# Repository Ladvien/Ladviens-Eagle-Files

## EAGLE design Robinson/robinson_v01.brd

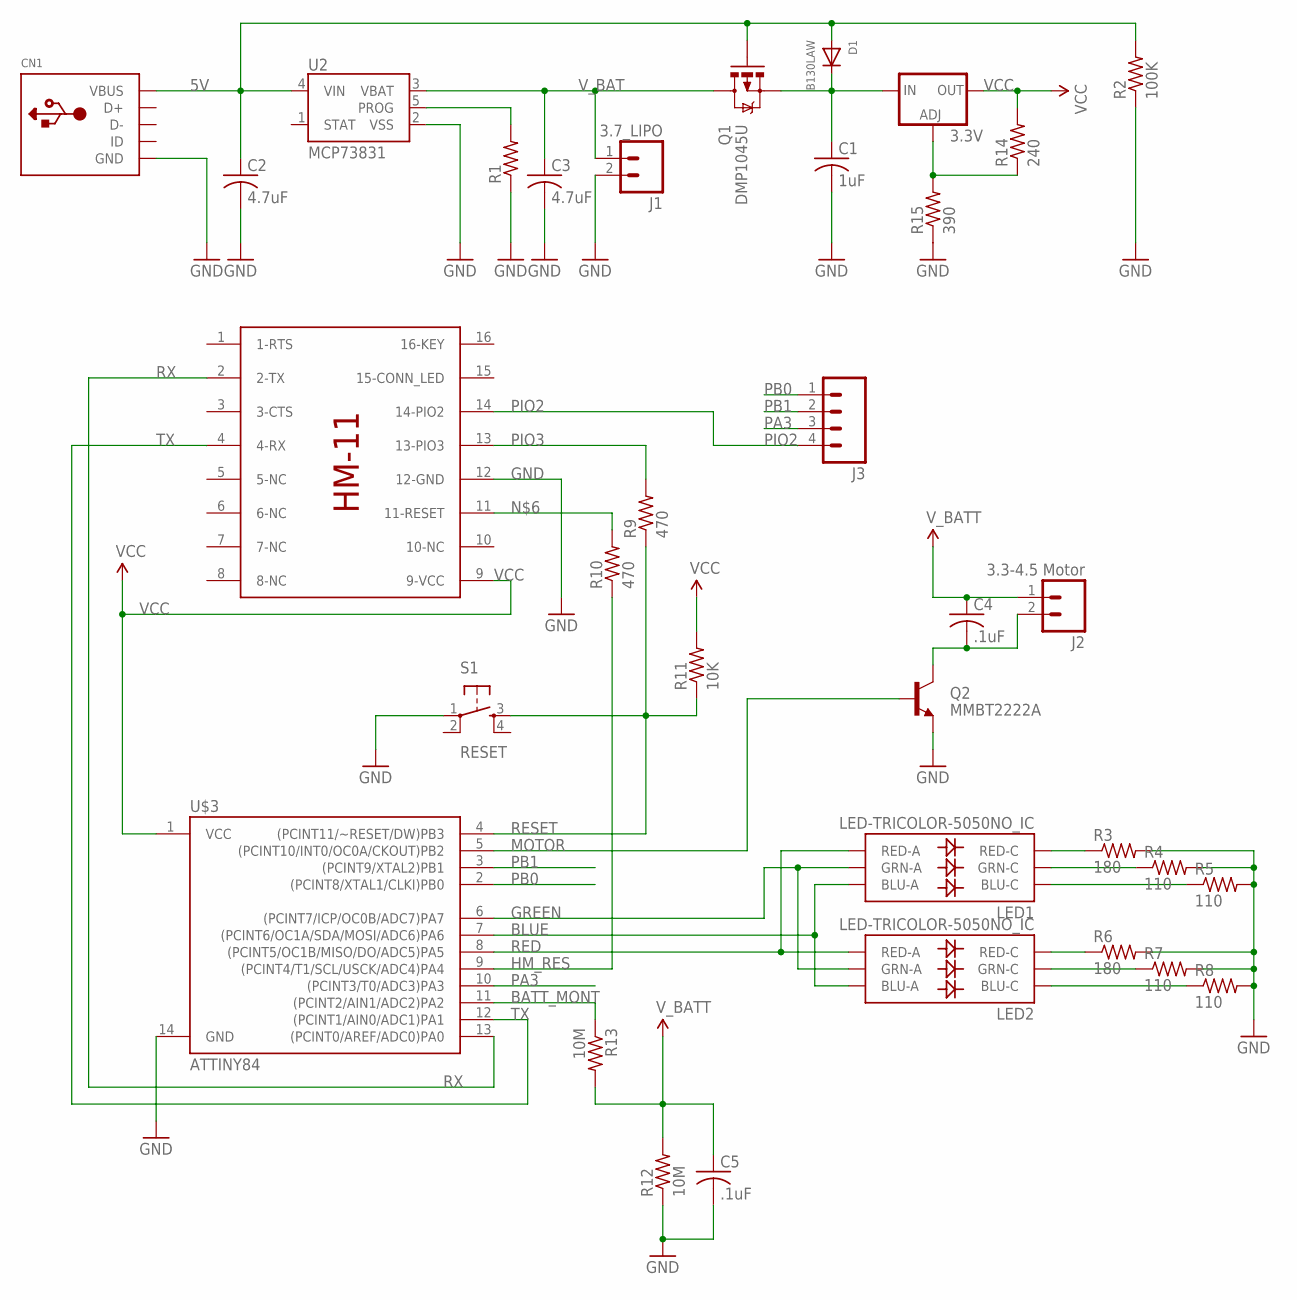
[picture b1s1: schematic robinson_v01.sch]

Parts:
3.3V: V_REG_317SMD; SOT223
C1: 1uF; C0805
C2, C3: 4.7uF; C0805
C4, C5: .1uF; C0805
CN1: USBMINIB; USB-MINIB
D1: B130LAW; SOD-123
J1: 3.7_LIPO; 1X02
J2: 3.3-4.5 Motor; 1X02
J3: M04PTH; 1X04
LED1, LED2: LED-TRICOLOR-5050NO_IC; LED-TRICOLOR-5050
Q1: DMP1045U; SOT23-3
Q2: MMBT2222A; SOT23-3
R1: R-US_R0805; R0805
R2: 100K; R0805
R3, R6: 180; R0805
R4, R5, R7, R8: 110; R0805
R9, R10: 470; R0805
R11: 10K; R0805
R12, R13: 10M; R0805
R14: 240; R0805
R15: 390; R0805
S1: RESET; TACTILE-SWITCH-SMD
U2: MCP73831; SOT23-5
U$1: HM-11
U$3: ATTINY84; SO14

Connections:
5V: C2.1, CN1.VBUS, D1.A, Q1.1 (G), R2.2, U2.4 (VIN)
BATT_MONT: R13.1, U$3.11 ((PCINT2/AIN1/ADC2)PA2)
BLUE: LED1.3 (BLU-A), LED2.3 (BLU-A), U$3.7 ((PCINT6/OC1A/SDA/MOSI/ADC6)PA6)
GND: C1.2, C2.2, C3.2, C5.2, CN1.GND, J1.2, Q2.2 (E), R1.1, R2.1, R3.2, R4.2, R5.2, R6.2, R7.2, R8.2, R12.1, R15.1, S1.1, U2.2 (VSS), U$1.12 (12-GND), U$3.14 (GND); also elsewhere on the board
GREEN: LED1.1 (GRN-A), LED2.1 (GRN-A), U$3.6 ((PCINT7/ICP/OC0B/ADC7)PA7)
HM_RES: R10.1, U$3.9 ((PCINT4/T1/SCL/USCK/ADC4)PA4)
MOTOR: Q2.1 (B), U$3.5 ((PCINT10/INT0/OC0A/CKOUT)PB2)
unnamed: R10.2, U$1.11 (11-RESET)
unnamed: C4.2, J2.2, Q2.3 (C)
unnamed: 3.3V.1 (ADJ), R14.1, R15.2
unnamed: LED1.5 (RED-C), R3.1
unnamed: 3.3V.3 (IN), C1.1, D1.C, Q1.2 (S)
unnamed: R1.2, U2.5 (PROG)
unnamed: LED1.6 (GRN-C), R4.1
unnamed: LED1.4 (BLU-C), R5.1
unnamed: LED2.5 (RED-C), R6.1
unnamed: LED2.6 (GRN-C), R7.1
unnamed: LED2.4 (BLU-C), R8.1
PA3: J3.3, U$3.10 ((PCINT3/T0/ADC3)PA3)
PB0: J3.1, U$3.2 ((PCINT8/XTAL1/CLKI)PB0)
PB1: J3.2, U$3.3 ((PCINT9/XTAL2)PB1)
PIO2: J3.4, U$1.14 (14-PIO2)
PIO3: R9.2, U$1.13 (13-PIO3)
RED: LED1.2 (RED-A), LED2.2 (RED-A), U$3.8 ((PCINT5/OC1B/MISO/DO/ADC5)PA5)
RESET: R9.1, R11.1, S1.3, U$3.4 ((PCINT11/~RESET/DW)PB3)
RX: U$1.2 (2-TX), U$3.13 ((PCINT0/AREF/ADC0)PA0)
TX: U$1.4 (4-RX), U$3.12 ((PCINT1/AIN0/ADC1)PA1)
VCC: 3.3V.2 (OUT), R11.2, R14.2, U$1.9 (9-VCC), U$3.1 (VCC); also elsewhere on the board
V_BAT: C3.1, J1.1, Q1.3 (D), U2.3 (VBAT)
V_BATT: C4.1, C5.1, J2.1, R12.2, R13.2

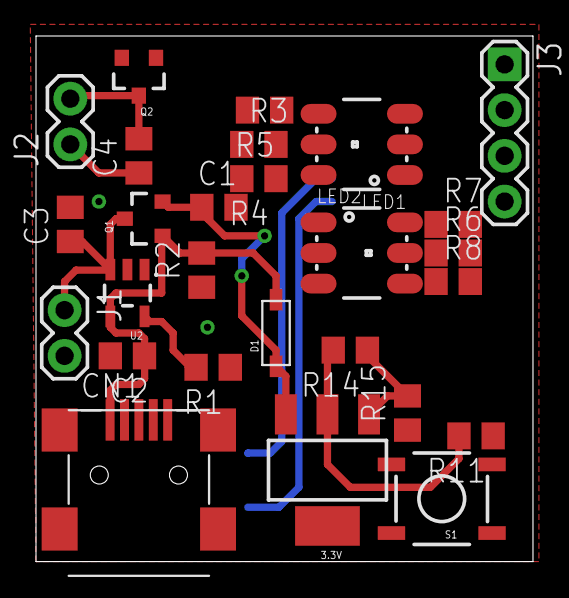
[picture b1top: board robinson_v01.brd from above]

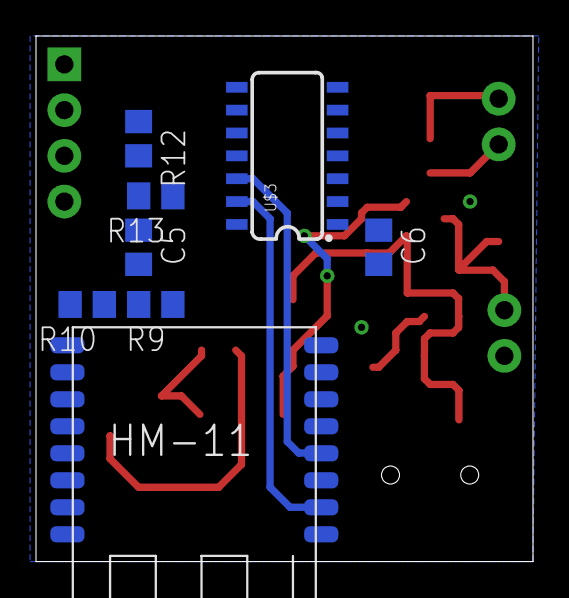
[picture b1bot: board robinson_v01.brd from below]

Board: 2 copper layers, 27.6 x 29.2 mm, 35 parts (8 on the bottom side), 30 nets.

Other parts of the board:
C6: 4.7uF; C0805

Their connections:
GND: C6.2; also elsewhere on the board
VCC: C6.1; also elsewhere on the board

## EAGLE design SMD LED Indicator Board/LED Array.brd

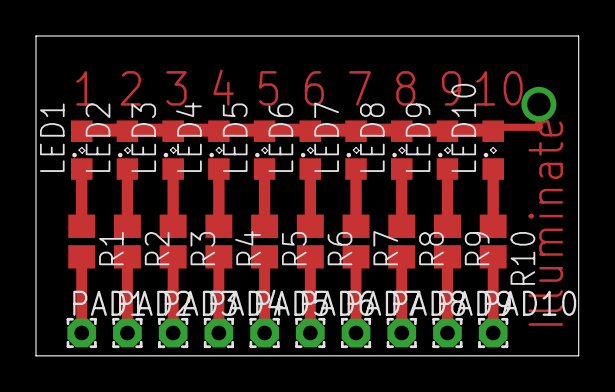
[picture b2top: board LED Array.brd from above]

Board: 2 copper layers, 30.1 x 17.8 mm, 30 parts (0 on the bottom side), 21 nets.

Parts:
LED1, LED2, LED3, LED4, LED5, LED6, LED7, LED8, LED9, LED10: SML0805
PAD1, PAD2, PAD3, PAD4, PAD5, PAD6, PAD7, PAD8, PAD9, PAD10: 1,6/0,8
R1, R2, R3, R4, R5, R6, R7, R8, R9, R10: R0805

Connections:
GND: LED1.A, LED2.A, LED3.A, LED4.A, LED5.A, LED6.A, LED7.A, LED8.A, LED9.A, LED10.A
unnamed: LED1.C, R1.1
unnamed: PAD1.1, R1.2
unnamed: PAD2.1, R2.2
unnamed: LED2.C, R2.1
unnamed: PAD3.1, R3.2
unnamed: LED3.C, R3.1
unnamed: PAD4.1, R4.2
unnamed: LED4.C, R4.1
unnamed: LED5.C, R5.1
unnamed: PAD5.1, R5.2
unnamed: PAD6.1, R6.2
unnamed: LED6.C, R6.1
unnamed: LED7.C, R7.1
unnamed: PAD7.1, R7.2
unnamed: PAD8.1, R8.2
unnamed: LED8.C, R8.1
unnamed: LED9.C, R9.1
unnamed: PAD9.1, R9.2
unnamed: PAD10.1, R10.2
unnamed: LED10.C, R10.1

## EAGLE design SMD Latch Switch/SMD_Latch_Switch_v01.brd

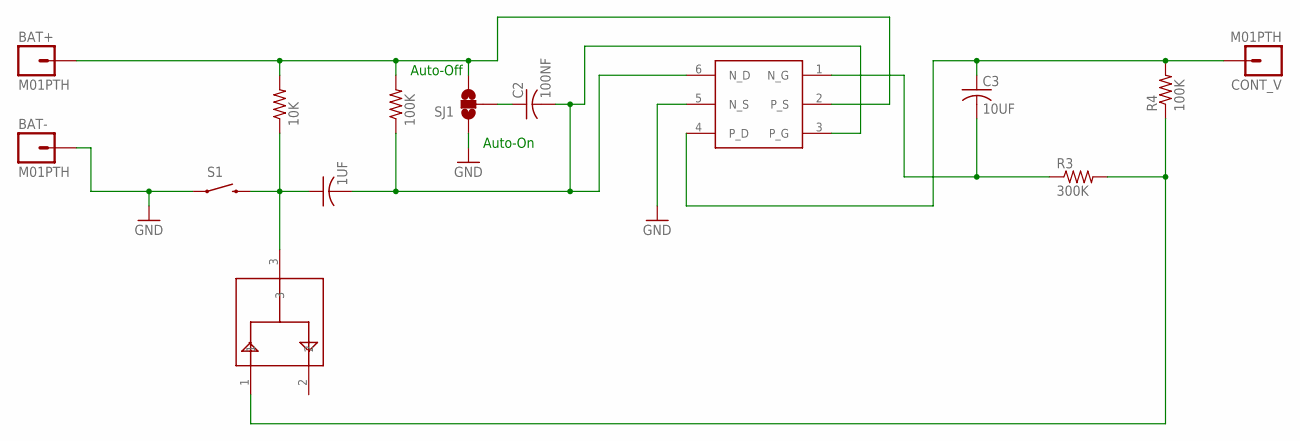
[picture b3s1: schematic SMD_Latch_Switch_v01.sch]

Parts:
1UF: 1UF; C0402
10K: 10K; R0402
100K: 100K; R0402
BAT+: M01PTH; 1X01
BAT-: M01PTH; 1X01
C2: 100NF; C0402
C3: 10UF; C0805
CONT_V: M01PTH; 1X01
R3: 300K; R0402
R4: 100K; R0402
S1: SWITCH-MOMENTARY-2SMD; TACTILE_SWITCH_SMD
SJ1: SOLDERJUMPER_2WAYPASTE1&2; SJ_3_PASTE1&2
U$1: SI3588DV; SOT23-6
U$2: BAV99; SOT23

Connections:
GND: BAT-.1, S1.1, SJ1.1, U$1.5 (N_S)
unnamed: 10K.2, 100K.2, BAT+.1, SJ1.3, U$1.2 (P_S)
unnamed: 1UF.1, 10K.1, S1.3 (2), U$2.3
unnamed: C2.1, SJ1.2
unnamed: 1UF.2, 100K.1, C2.2, U$1.3 (P_G), U$1.6 (N_D)
unnamed: R3.2, R4.1, U$2.1
unnamed: C3.1, CONT_V.1, R4.2, U$1.4 (P_D)
unnamed: C3.2, R3.1, U$1.1 (N_G)

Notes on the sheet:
Auto-On
Auto-Off

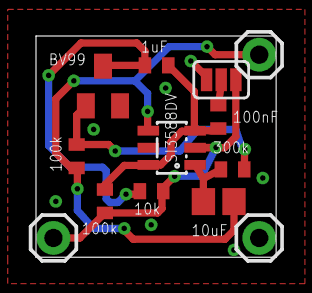
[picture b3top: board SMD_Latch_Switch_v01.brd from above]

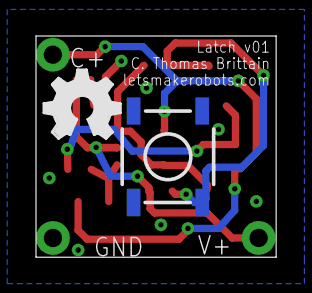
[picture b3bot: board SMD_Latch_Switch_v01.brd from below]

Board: 2 copper layers, 13.3 x 12.3 mm, 15 parts (2 on the bottom side), 8 nets.

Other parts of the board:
U$3: OSHW_FILLX150_NOTEXT

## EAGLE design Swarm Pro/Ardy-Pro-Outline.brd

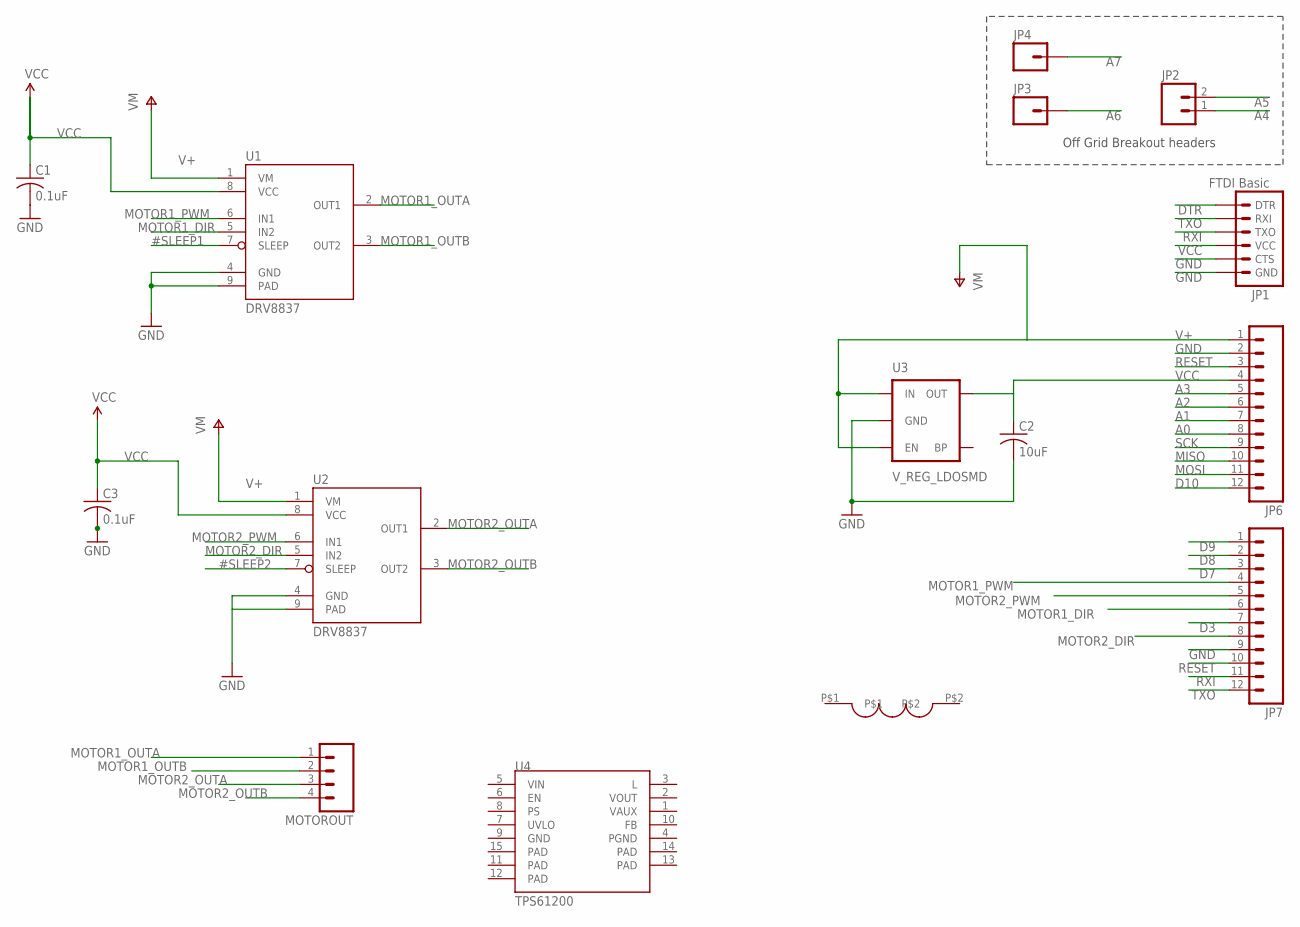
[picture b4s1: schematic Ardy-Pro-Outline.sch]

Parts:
2.2UH: 2.2uh; PEBBLE_VLF4012A
C1, C3: 0.1uF; C0402
C2: 10uF; C0805
JP1: FTDI Basic; 1X06
JP2: M02PTH; 1X02
JP3, JP4: M01PTH; 1X01
JP6, JP7: M12PTH; 1X12
MOTOROUT: M04PTH; 1X04
U1, U2: DRV8837; WSON-8
U3: V_REG_LDOSMD; SOT23-5
U4: TPS61200; QFN-10_PAD

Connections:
#SLEEP1: U1.7 (SLEEP)
#SLEEP2: U2.7 (SLEEP)
A0: JP6.8
A1: JP6.7
A2: JP6.6
A3: JP6.5
A4: JP2.1
A5: JP2.2
A6: JP3.1
A7: JP4.1
D3: JP7.7
D7: JP7.3
D8: JP7.2
D9: JP7.1
D10: JP6.12
DTR: JP1.1 (DTR)
GND: C1.2, C2.2, C3.2, JP1.5 (CTS), JP1.6 (GND), JP6.2, JP7.9, U1.4 (GND), U1.9 (PAD), U2.4 (GND), U3.2 (GND)
MISO: JP6.10
MOSI: JP6.11
MOTOR1_DIR: JP7.6, U1.5 (IN2)
MOTOR1_OUTA: MOTOROUT.1, U1.2 (OUT1)
MOTOR1_OUTB: MOTOROUT.2, U1.3 (OUT2)
MOTOR1_PWM: JP7.4, U1.6 (IN1)
MOTOR2_DIR: JP7.8, U2.5 (IN2)
MOTOR2_OUTA: MOTOROUT.3, U2.2 (OUT1)
MOTOR2_OUTB: MOTOROUT.4, U2.3 (OUT2)
MOTOR2_PWM: JP7.5, U2.6 (IN1)
RESET: JP6.3, JP7.10
RXI: JP1.3 (TXO), JP7.11
SCK: JP6.9
TXO: JP1.2 (RXI), JP7.12
V+: JP6.1, U1.1 (VM), U2.1 (VM), U3.1 (IN), U3.3 (EN)
VCC: C1.1, C2.1, C3.1, JP1.4 (VCC), JP6.4, U1.8 (VCC), U2.8 (VCC), U3.5 (OUT)

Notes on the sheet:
Off Grid Breakout headers

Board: 2 copper layers, 15 parts (6 on the bottom side), 14 nets, no tracks yet.

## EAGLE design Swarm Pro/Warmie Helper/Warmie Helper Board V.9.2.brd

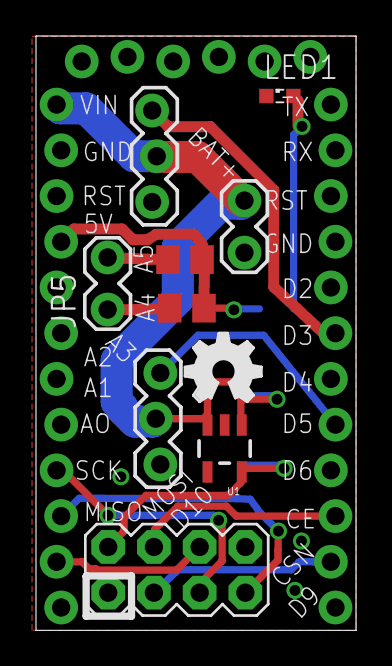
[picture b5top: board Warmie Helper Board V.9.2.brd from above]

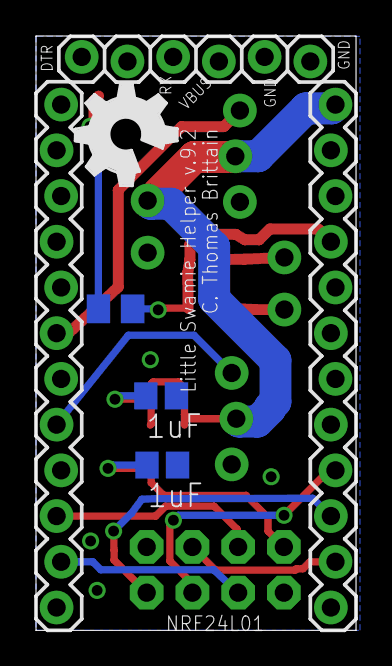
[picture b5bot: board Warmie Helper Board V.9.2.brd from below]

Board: 2 copper layers, 17.8 x 33.0 mm, 17 parts (7 on the bottom side), 14 nets.

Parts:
BATTERY: 1X02_LOCK
C1, C2: 1uF; C0805
JP1, JP2: M12LOCK; 1X12_LOCK
JP3, JP4: 1X03_LOCK
JP5: 1X02_LOCK
JP6: 1X06_LOCK
LED1: SML0603
NRF24L01: M04X2; 2X4
R1, R2: 4.7k; M0805
R3: 330; M0805
U1: V_REG_LDOSMD; SOT23-5
U$2: OSHW_FILLX200_NOTEXT
U$3: OSHW_FILLX150_NOTEXT

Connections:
5V: JP1.9, R1.1, R2.1, R3.2
A4: JP5.1, R1.2
A5: JP5.2, R2.2
CE: JP2.2, NRF24L01.6
CSN: JP2.3, NRF24L01.5
D3: JP2.7, JP3.3
D5: JP2.5, JP4.1
GND: BATTERY.2, C1.2, C2.2, JP1.11, JP2.9, JP3.1, JP4.3, JP6.1, JP6.2, LED1.C, NRF24L01.8, U1.2
MISO: JP1.3, NRF24L01.2
MOSI: JP1.2, NRF24L01.3
unnamed: LED1.A, R3.1
SCK: JP1.4, NRF24L01.4
V3.3: C1.1, NRF24L01.7, U1.5
VIN: BATTERY.1, C2.1, JP1.12, JP3.2, JP4.2, U1.1, U1.3

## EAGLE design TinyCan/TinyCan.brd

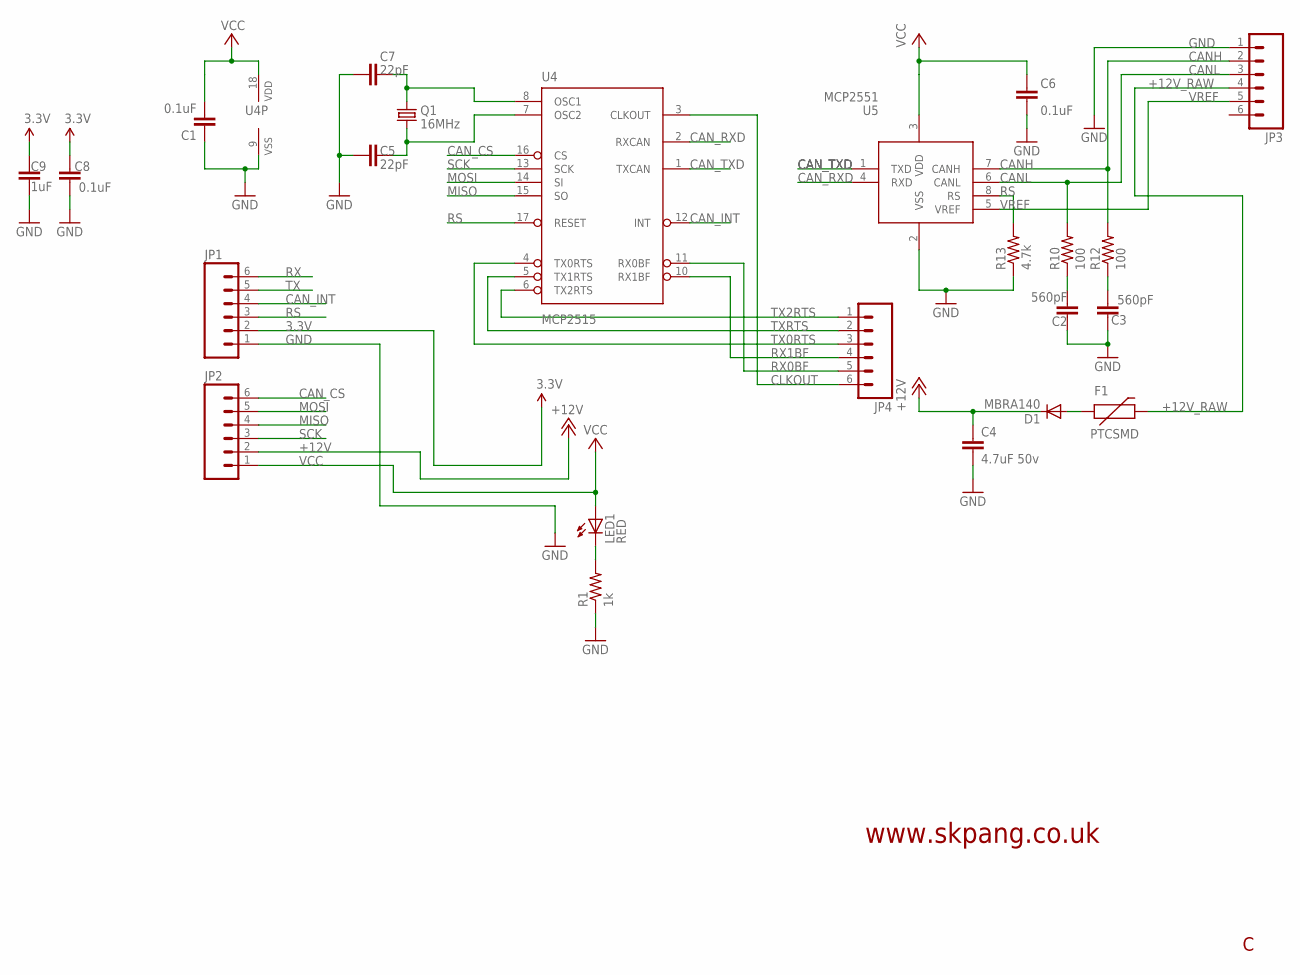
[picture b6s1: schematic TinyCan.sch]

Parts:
C1, C6, C8: 0.1uF; 0603-CAP
C2, C3: 560pF; 0603-CAP
C4: 4.7uF 50v; 0603-CAP
C5, C7: 22pF; 0603-CAP
C9: 1uF; 0603-CAP
D1: MBRA140; SMA-DIODE
F1: PTCSMD; PTC-1206
JP1, JP2, JP3, JP4: M06LOCK; 1X06_LOCK
LED1: RED; LED-0603
Q1: 16MHz; CRYSTAL-SMD-5X3
R1: 1k; 0603-RES
R10, R12: 100; 0603-RES
R13: 4.7k; 0603-RES
U4: MCP2515; SO-18W
U5: MCP2551; SO-08M

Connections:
3.3V: C8.2, C9.1, JP1.2
+12V: C4.1, D1.C, JP2.2
+12V_RAW: F1.2, JP3.4
CANH: JP3.2, R12.2, U5.7 (CANH)
CANL: JP3.3, R10.2, U5.6 (CANL)
CAN_CS: JP2.6, U4.16 (CS)
CAN_INT: JP1.4, U4.12 (INT)
CAN_RXD: U4.2 (RXCAN), U5.4 (RXD)
CAN_TXD: U4.1 (TXCAN), U5.1 (TXD)
CLKOUT: JP4.6, U4.3 (CLKOUT)
GND: C1.1, C2.1, C3.1, C4.2, C5.1, C6.1, C7.1, C8.1, C9.2, JP1.1, JP3.1, R1.1, R13.1, U4.9 (VSS), U5.2 (VSS)
MISO: JP2.4, U4.15 (SO)
MOSI: JP2.5, U4.14 (SI)
unnamed: LED1.C, R1.2
unnamed: C2.2, R10.1
unnamed: C3.2, R12.1
unnamed: D1.A, F1.1
unnamed: C7.2, Q1.3 (2), U4.8 (OSC1)
unnamed: C5.2, Q1.1, U4.7 (OSC2)
RS: JP1.3, R13.2, U4.17 (RESET), U5.8 (RS)
RX: JP1.6
RX0BF: JP4.5, U4.11 (RX0BF)
RX1BF: JP4.4, U4.10 (RX1BF)
SCK: JP2.3, U4.13 (SCK)
TX: JP1.5
TX0RTS: JP4.3, U4.4 (TX0RTS)
TX2RTS: JP4.1, U4.6 (TX2RTS)
TXRTS: JP4.2, U4.5 (TX1RTS)
VCC: C1.2, C6.2, JP2.1, LED1.A, U4.18 (VDD), U5.3 (VDD)
VREF: JP3.5, U5.5 (VREF)

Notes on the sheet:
www.skpang.co.uk

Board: 2 copper layers, 23 parts (0 on the bottom side), 28 nets, no tracks yet.

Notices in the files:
parts and their libraries:
SparkFun-DigitalIC: Licensing: Creative Commons ShareAlike 4.0 International - https://creativecommons.org/licenses/by-sa/4.0
SparkFun-Electromechanical: Licensing: CC v3.0 Share-Alike You are welcome to use this library for commercial purposes.
